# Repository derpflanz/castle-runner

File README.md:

# castle-runner

This is my hobby project in making a 6502 based 8-bit computer from scratch. The end goal is to have it run Castle Runner, a game I made many moons ago.

# CR Assembler

Castle Runner is built from scratch, including the assembler (new version, written in C). I created my own assembly language dialect to assemble the machine language code. That ML can then be written to a EEPROM. For which I built my own EEPROM programmer.

## Layout

By default, the RESET vector is set to $8000, which is the start of the ROM in the CR001 computer. The VirtualCR001 uses that as well by default. When programming the EEPROM, this vector is sent as the first two bytes and stored in $FFFC/$FFFD in the ROM.

Note that the assembler can have a DATA section at the start, which will cause to use another RESET vector to be written at the start of the .hex file.

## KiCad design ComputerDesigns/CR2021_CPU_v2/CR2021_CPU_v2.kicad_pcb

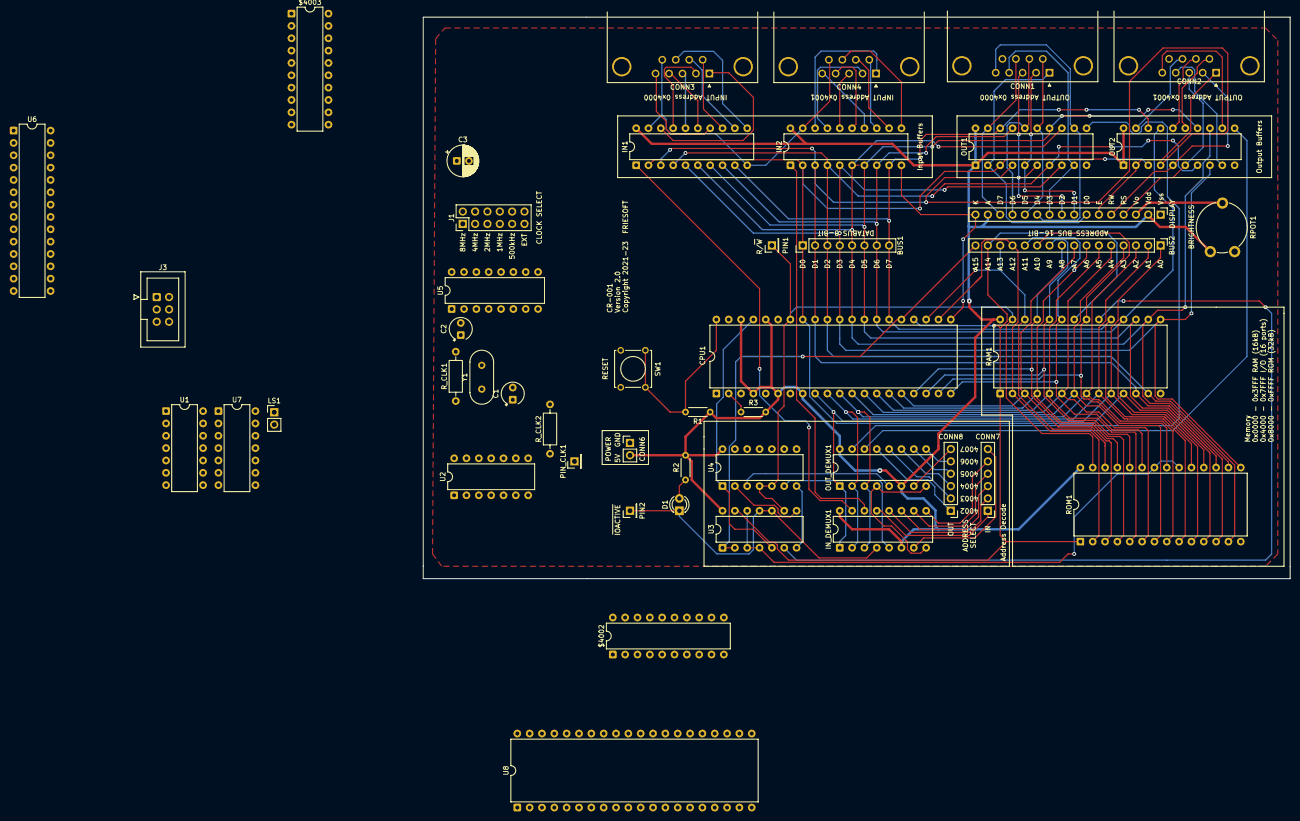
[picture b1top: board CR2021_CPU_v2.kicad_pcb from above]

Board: 2 copper layers, 178.4 x 115.6 mm, 47 parts (0 on the bottom side), 99 nets.

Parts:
$4002, $4003: 74LS273; DIP-20_W7.62mm
BUS1: DATABUS_8BIT; PinHeader_1x08_P2.54mm_Vertical
BUS2: ADDRBUS_16BIT; PinHeader_1x16_P2.54mm_Vertical
C1, C2: 22pF; CP_Radial_Tantal_D4.5mm_P2.50mm
C3: 100uF; CP_Radial_D6.3mm_P2.50mm
CONN1: OUT1; DSUB-9_Male_Horizontal_P2.77x2.84mm_EdgePinOffset9.90mm_Hou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
CONN2: OUT2; DSUB-9_Male_Horizontal_P2.77x2.84mm_EdgePinOffset9.90mm_Hou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
CONN3: IN1; DSUB-9_Male_Horizontal_P2.77x2.84mm_EdgePinOffset9.90mm_Hou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
CONN4: IN2; DSUB-9_Male_Horizontal_P2.77x2.84mm_EdgePinOffset9.90mm_Hou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
CONN5: Display; PinHeader_1x16_P2.54mm_Vertical
CONN6: +5V; PinHeader_1x02_P2.54mm_Vertical
CONN7: ADDRSEL_IN; PinHeader_1x06_P2.54mm_Vertical
CONN8: ADDRSEL_OUT; PinHeader_1x06_P2.54mm_Vertical
CPU1: WD65C02S; DIP-40_W15.24mm
D1: IO_Active; LED_D3.0mm
IN1, IN2: 74LS540; DIP-20_W7.62mm
IN_DEMUX1: 74LS138; DIP-16_W7.62mm
J1: Conn_02x06_Odd_Even; PinHeader_2x06_P2.54mm_Vertical
J3: Atmega328 Programmer Interface; IDC-Header_2x03_P2.54mm_Vertical
LS1: Speaker; PinHeader_1x02_P2.54mm_Vertical
OUT1, OUT2: 74LS273; DIP-20_W7.62mm
OUT_DEMUX1: 74LS138; DIP-16_W7.62mm
PIN1: R/!W; PinHeader_1x01_P2.54mm_Vertical
PIN2: !IO_Active; PinHeader_1x01_P2.54mm_Vertical
PIN_CLK1: EXT_CLK; PinHeader_1x01_P2.54mm_Vertical
R1: 1k; R_Axial_DIN0204_L3.6mm_D1.6mm_P5.08mm_Horizontal
R2: 330; R_Axial_DIN0204_L3.6mm_D1.6mm_P5.08mm_Horizontal
R3: 3.3k; R_Axial_DIN0204_L3.6mm_D1.6mm_P5.08mm_Horizontal
RAM1: 32 kB RAM; DIP-28_W15.24mm
ROM1: ROM ZIF Socket; DIP-28_W15.24mm
RPOT1: 10k; Potentiometer_Piher_PT-10-V10_Vertical
R_CLK1: 10M; R_Axial_DIN0207_L6.3mm_D2.5mm_P10.16mm_Horizontal
R_CLK2: 22; R_Axial_DIN0207_L6.3mm_D2.5mm_P10.16mm_Horizontal
SW1: RESET; SW_Tactile_Straight_KSL0Axx1LFTR
U1, U7: LM324; DIP-14_W7.62mm
U2: 74HCU04; DIP-14_W7.62mm
U3, U4: 7400; DIP-14_W7.62mm
U5: 74LS163; DIP-16_W7.62mm
U6: ATmega328-P; DIP-28_W7.62mm
U8: W65C22NxP; DIP-40_W15.24mm
Y1: Crystal 8MHz; Crystal_HC18-U_Vertical

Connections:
$4002_OUT: $4002.11 (Cp), CONN8.1, OUT_DEMUX1.13 (O2), U6.4 (PD2)
$4003_OUT: $4003.11 (Cp), CONN8.2, OUT_DEMUX1.12 (O3), U6.5 (PD3)
+5V: $4002.1 (~Mr), $4002.20 (VCC), $4003.1 (~Mr), $4003.20 (VCC), C3.1, CONN5.2, CONN5.15, CONN6.2, CPU1.4 (~IRQ), CPU1.6 (~NMI), CPU1.8 (VCC), CPU1.36 (BE), CPU1.38 (~SO), IN1.20 (VCC), IN2.20 (VCC), IN_DEMUX1.6 (E3), IN_DEMUX1.16 (VCC), J3.2 (VCC), OUT1.1 (~Mr), OUT1.20 (VCC), OUT2.1 (~Mr), OUT2.20 (VCC), OUT_DEMUX1.6 (E3), OUT_DEMUX1.16 (VCC), R1.1, R2.2, R3.2, RAM1.28 (VCC), ROM1.28 (VCC), RPOT1.3, U1.4 (V+), U2.14 (VCC), U3.14 (VCC), U4.14 (VCC), U5.1 (~MR), U5.7 (CEP), U5.9 (~PE), U5.10 (CET), U5.16 (VCC), U6.7 (VCC), U6.20 (AVCC)
/$4000_IN: IN1.1 (G1), IN_DEMUX1.15 (O0)
/$4000_OUT: OUT1.11 (Cp), OUT_DEMUX1.15 (O0)
/$4001_IN: IN2.1 (G1), IN_DEMUX1.14 (O1)
/$4001_OUT: OUT2.11 (Cp), OUT_DEMUX1.14 (O1)
/A14: BUS2.15, CPU1.24 (A14), RAM1.1 (A14), RAM1.22 (~OE), ROM1.1 (A14), U3.13
/A15: BUS2.16, CPU1.25 (A15), U3.1, U3.2
/Sound/PWM_Sound_Out_Voice2: J3.4 (MOSI), U6.17 (PB3)
CLK: CPU1.37 (PHI2), J1.2, J1.4, J1.6, J1.8, J1.10, J1.12, U3.5, U3.9
DATA0: $4002.3 (D0), $4003.3 (D0), BUS1.1, CPU1.33 (D0), IN1.18 (Y0), IN2.18 (Y0), OUT1.3 (D0), OUT2.3 (D0), RAM1.11 (Q0), ROM1.11 (D0), U6.23 (PC0), U8.33 (D0)
DATA1: $4002.4 (D1), $4003.4 (D1), BUS1.2, CPU1.32 (D1), IN1.17 (Y1), IN2.17 (Y1), OUT1.4 (D1), OUT2.4 (D1), RAM1.12 (Q1), ROM1.12 (D1), U6.24 (PC1), U8.32 (D1)
DATA2: $4002.7 (D2), $4003.7 (D2), BUS1.3, CPU1.31 (D2), IN1.16 (Y2), IN2.16 (Y2), OUT1.7 (D2), OUT2.7 (D2), RAM1.13 (Q2), ROM1.13 (D2), U6.25 (PC2), U8.31 (D2)
DATA3: $4002.8 (D3), $4003.8 (D3), BUS1.4, CPU1.30 (D3), IN1.15 (Y3), IN2.15 (Y3), OUT1.8 (D3), OUT2.8 (D3), RAM1.15 (Q3), ROM1.15 (D3), U6.26 (PC3), U8.30 (D3)
DATA4: $4002.13 (D4), $4003.13 (D4), BUS1.5, CPU1.29 (D4), IN1.14 (Y4), IN2.14 (Y4), OUT1.13 (D4), OUT2.13 (D4), RAM1.16 (Q4), ROM1.16 (D4), U6.27 (PC4), U8.29 (D4)
DATA5: $4002.14 (D5), $4003.14 (D5), BUS1.6, CPU1.28 (D5), IN1.13 (Y5), IN2.13 (Y5), OUT1.14 (D5), OUT2.14 (D5), RAM1.17 (Q5), ROM1.17 (D5), U6.28 (PC5), U8.28 (D5)
DATA6: $4002.17 (D6), $4003.17 (D6), BUS1.7, CPU1.27 (D6), IN1.12 (Y6), IN2.12 (Y6), OUT1.17 (D6), OUT2.17 (D6), RAM1.18 (Q6), ROM1.18 (D6), U6.2 (PD0), U8.27 (D6)
DATA7: $4002.18 (D7), $4003.18 (D7), BUS1.8, CPU1.26 (D7), IN1.11 (Y7), IN2.11 (Y7), OUT1.18 (D7), OUT2.18 (D7), RAM1.19 (Q7), ROM1.19 (D7), U6.3 (PD1), U8.26 (D7)
GND: $4002.10 (GND), $4003.10 (GND), C1.2, C2.2, C3.2, CONN1.9, CONN2.9, CONN3.9, CONN4.9, CONN5.1, CONN5.16, CONN6.1, CPU1.21 (GND), IN1.10 (GND), IN1.19 (G2), IN2.10 (GND), IN2.19 (G2), IN_DEMUX1.8 (GND), J3.6 (GND), LS1.2, OUT1.10 (GND), OUT2.10 (GND), OUT_DEMUX1.8 (GND), RAM1.14 (GND), ROM1.14 (GND), RPOT1.1, SW1.2 (B), U1.11 (V-), U2.7 (GND), U3.7 (GND), U4.7 (GND), U5.3 (D0), U5.4 (D1), U5.5 (D2), U5.6 (D3), U5.8 (GND), U6.8 (GND), U6.22 (GND)
unnamed: BUS2.1, CPU1.9 (A0), IN_DEMUX1.1 (A0), OUT_DEMUX1.1 (A0), RAM1.10 (A0), ROM1.10 (A0)
unnamed: BUS2.2, CPU1.10 (A1), IN_DEMUX1.2 (A1), OUT_DEMUX1.2 (A1), RAM1.9 (A1), ROM1.9 (A1)
unnamed: BUS2.3, CPU1.11 (A2), IN_DEMUX1.3 (A2), OUT_DEMUX1.3 (A2), RAM1.8 (A2), ROM1.8 (A2)
unnamed: BUS2.4, CPU1.12 (A3), RAM1.7 (A3), ROM1.7 (A3)
unnamed: BUS2.5, CPU1.13 (A4), RAM1.6 (A4), ROM1.6 (A4)
unnamed: BUS2.6, CPU1.14 (A5), RAM1.5 (A5), ROM1.5 (A5)
unnamed: BUS2.7, CPU1.15 (A6), RAM1.4 (A6), ROM1.4 (A6)
unnamed: BUS2.8, CPU1.16 (A7), RAM1.3 (A7), ROM1.3 (A7)
unnamed: BUS2.9, CPU1.17 (A8), RAM1.25 (A8), ROM1.25 (A8)
unnamed: BUS2.10, CPU1.18 (A9), RAM1.24 (A9), ROM1.24 (A9)
unnamed: BUS2.11, CPU1.19 (A10), RAM1.21 (A10), ROM1.21 (A10)
unnamed: BUS2.12, CPU1.20 (A11), RAM1.23 (A11), ROM1.23 (A11)
unnamed: BUS2.13, CPU1.22 (A12), RAM1.2 (A12), ROM1.2 (A12)
unnamed: BUS2.14, CPU1.23 (A13), RAM1.26 (A13), ROM1.26 (A13)
unnamed: C1.1, R_CLK1.1, U2.9, Y1.1
unnamed: C2.1, R_CLK1.2, R_CLK2.2, Y1.2
unnamed: CONN1.1, CONN5.7, OUT1.2 (Q0)
unnamed: CONN1.2, CONN5.8, OUT1.5 (Q1)
unnamed: CONN1.3, CONN5.9, OUT1.6 (Q2)
unnamed: CONN1.4, CONN5.10, OUT1.9 (Q3)
unnamed: CONN1.5, CONN5.11, OUT1.12 (Q4)
unnamed: CONN1.6, CONN5.12, OUT1.15 (Q5)
unnamed: CONN1.7, CONN5.13, OUT1.16 (Q6)
unnamed: CONN1.8, CONN5.14, OUT1.19 (Q7)
unnamed: CONN2.1, CONN5.6, OUT2.2 (Q0)
unnamed: CONN2.2, CONN5.5, OUT2.5 (Q1)
unnamed: CONN2.3, CONN5.4, OUT2.6 (Q2)
unnamed: CONN2.4, OUT2.9 (Q3)
unnamed: CONN2.5, OUT2.12 (Q4)
unnamed: CONN2.6, OUT2.15 (Q5)
unnamed: CONN2.7, OUT2.16 (Q6)
unnamed: CONN2.8, OUT2.19 (Q7)
unnamed: CONN3.1, IN1.2 (A0)
unnamed: CONN3.2, IN1.3 (A1)
unnamed: CONN3.3, IN1.4 (A2)
unnamed: CONN3.4, IN1.5 (A3)
unnamed: CONN3.5, IN1.6 (A4)
unnamed: CONN3.6, IN1.7 (A5)
unnamed: CONN3.7, IN1.8 (A6)
unnamed: CONN3.8, IN1.9 (A7)
unnamed: CONN4.1, IN2.2 (A0)
unnamed: CONN4.2, IN2.3 (A1)
unnamed: CONN4.3, IN2.4 (A2)
unnamed: CONN4.4, IN2.5 (A3)
unnamed: CONN4.5, IN2.6 (A4)
unnamed: CONN4.6, IN2.7 (A5)
unnamed: CONN4.7, IN2.8 (A6)
unnamed: CONN4.8, IN2.9 (A7)
unnamed: CONN5.3, RPOT1.2
unnamed: CONN7.1, IN_DEMUX1.13 (O2)
unnamed: CONN7.2, IN_DEMUX1.12 (O3)
unnamed: CONN7.3, IN_DEMUX1.11 (O4)
unnamed: CONN7.4, IN_DEMUX1.10 (O5)
unnamed: CONN7.5, IN_DEMUX1.9 (O6)
unnamed: CONN7.6, IN_DEMUX1.7 (O7)
unnamed: CONN8.3, OUT_DEMUX1.11 (O4)
unnamed: CONN8.4, OUT_DEMUX1.10 (O5)
unnamed: CONN8.5, OUT_DEMUX1.9 (O6)
unnamed: CONN8.6, OUT_DEMUX1.7 (O7)
unnamed: CPU1.2 (RDY), R3.1
unnamed: CPU1.40 (~RESET), R1.2, SW1.1 (A)
unnamed: D1.2 (A), R2.1
unnamed: D1.1 (K), IN_DEMUX1.4 (E1), OUT_DEMUX1.4 (E1), PIN2.1, U3.11
unnamed: IN_DEMUX1.5 (E2), U3.10, U4.6
unnamed: J1.1, R_CLK2.1, U2.8, U5.2 (CP)
unnamed: J1.3, U5.14 (Q0)
unnamed: J1.5, U5.13 (Q1)
unnamed: J1.7, U5.12 (Q2)
unnamed: J1.9, U5.11 (Q3)
unnamed: J1.11, PIN_CLK1.1
unnamed: J3.1 (MISO), U6.18 (PB4)
unnamed: J3.5 (RST), U6.1 (~RESET/PC6)
unnamed: J3.3 (SCK), U6.19 (PB5)
unnamed: LS1.1, U1.7
unnamed: OUT_DEMUX1.5 (E2), U3.8
unnamed: RAM1.20 (~CS), U3.6
unnamed: ROM1.20 (~CS), ROM1.22 (~OE), U3.3, U3.4, U3.12
unnamed: U1.5 (+), U7.1, U7.2 (-)
R/!W: CPU1.34 (R/~W), PIN1.1, RAM1.27 (~WE), ROM1.27 (~WE), U4.4, U4.5

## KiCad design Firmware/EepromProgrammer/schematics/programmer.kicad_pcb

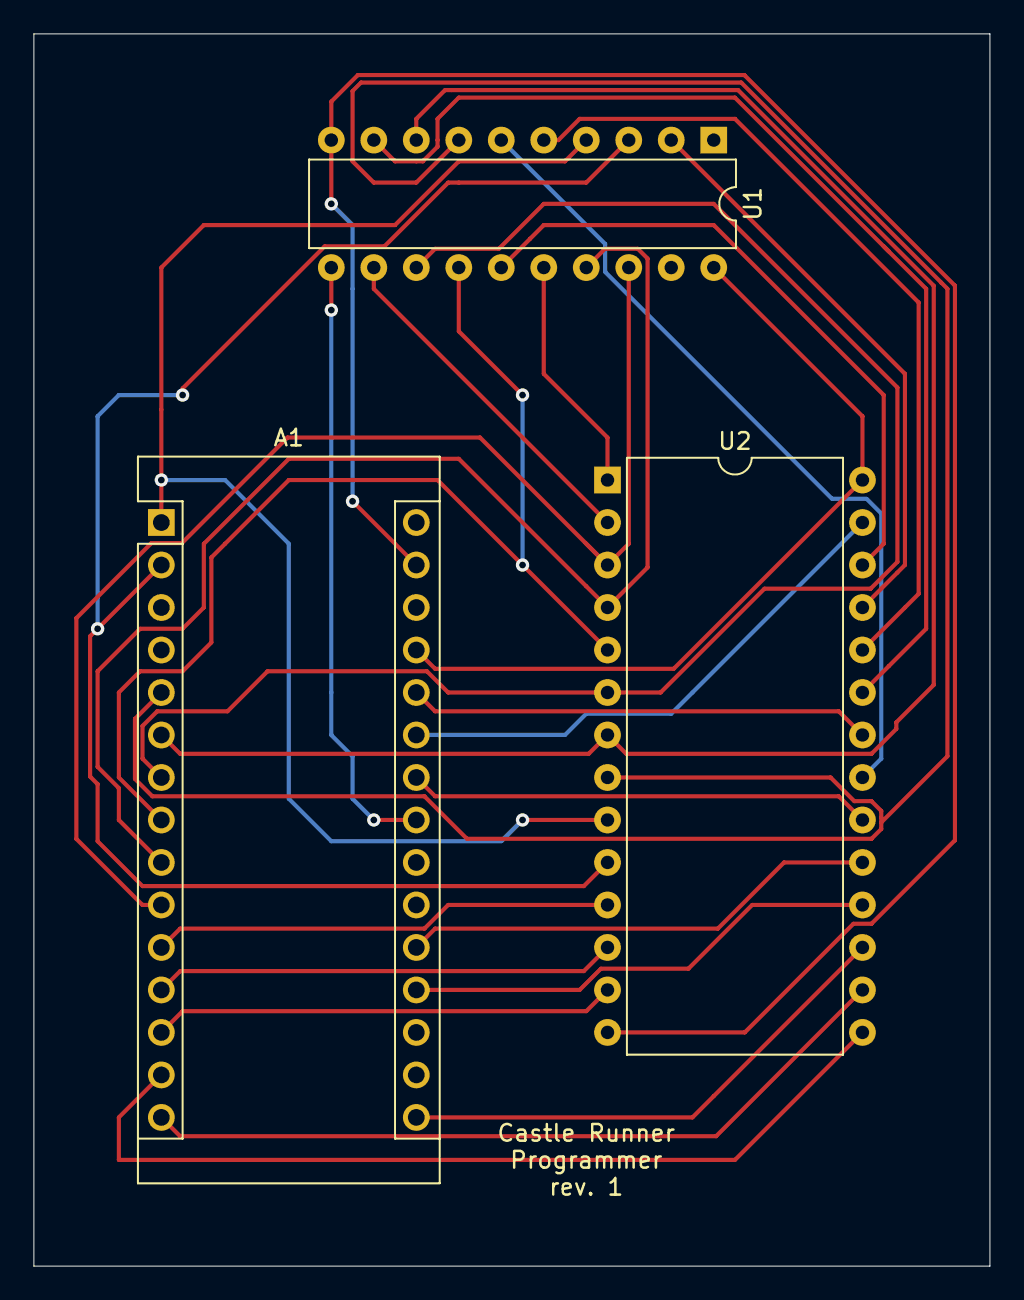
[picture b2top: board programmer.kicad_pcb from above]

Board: 2 copper layers, 57.2 x 73.7 mm, 3 parts (0 on the bottom side), 29 nets.

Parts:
A1: Arduino_Nano_v3.x; Arduino_Nano
U1: 74LS273; DIP-20_W7.62mm
U2: KM62256CLP; DIP-28_W15.24mm

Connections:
unnamed: A1.1, U1.4, U2.9
unnamed: A1.2, U1.3, U2.10
unnamed: A1.5, U1.7, U2.8
unnamed: A1.6, U1.8, U2.7
unnamed: A1.7, U1.13, U2.6
unnamed: A1.8, U1.14, U2.5
unnamed: A1.9, U1.17, U2.4
unnamed: A1.10, U1.18, U2.3
unnamed: A1.11, U2.11
unnamed: A1.12, U2.12
unnamed: A1.13, U2.13
unnamed: A1.14, U2.15
unnamed: A1.15, U2.16
unnamed: A1.16, U2.17
unnamed: A1.19, U2.18
unnamed: A1.20, U2.19
unnamed: A1.23, U1.11
unnamed: A1.24, U2.20
unnamed: A1.25, U2.27
unnamed: A1.26, U2.22
unnamed: A1.27, U1.1, U1.20, U2.28
unnamed: A1.29, U1.10, U2.14
unnamed: U1.2, U2.25
unnamed: U1.5, U2.24
unnamed: U1.6, U2.21
unnamed: U1.9, U2.23
unnamed: U1.12, U2.2
unnamed: U1.15, U2.26
unnamed: U1.16, U2.1

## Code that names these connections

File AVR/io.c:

#include "io.h"

// PD4 = ~R/W
// PD5 = CTRL_REG
// PD6 = DATA_REG
// PC0-PC5,PD0-PD1 = DATA

void init_io() {
    DDRD &= ~(
        // Set R/!W, DR and CR as INPUTs (no pullup resistor)
        (1 << DDD2) | (1 << DDD3) | (1 << DDD4) | 

        // Set D6 and D7 as INPUTs (no pullup)
        (1 << DDD0) | (1 << DDD1)
    );

    DDRC &= ~(
        // Set D0-5 as INPUTs (no pullup)
        (1 << DDC0) | (1 << DDC1) | (1 << DDC2) | 
        (1 << DDC3) | (1 << DDC4) | (1 << DDC5) 
    )
}

uint8_t rw() {
    return (PIND & (1 << PD4) ? 1 : 0);
}

uint8_t dr() {
    return (PIND & (1 << PD2) ? 1 : 0);
}

uint8_t cr() {
    return (PIND & (1 << PD3) ? 1 : 0);
}

uint8_t data() {
    uint8_t d = 0;

    // read PC0-5
    d |= (PINC & 0b00111111);
    // read PD0-1
    d |= ((PIND & 0b00000011) << 6);

    return d;
}

struct state read_state() {
    struct state io_state;

    io_state.rw = rw();
    io_state.dr = dr();
    io_state.cr = cr();
    io_state.data = data();
    
    io_state.reg_select = REG_NONE;

    if (io_state.dr == 1 && io_state.cr == 0) {
        io_state.reg_select = REG_DATA;
    }

    if (io_state.dr == 0 && io_state.cr == 1) {
        io_state.reg_select = REG_CTRL;
    }

    return io_state;
}

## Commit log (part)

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2021-01-10 implement EEPROM read
2021-01-10 add eeprom.py
2021-01-17 Working version
2021-01-17 cleanup
2021-01-17 Fix SYNC at startup
2021-01-30 Add port to command
2021-01-30 Bigfixes
2021-01-30 Write 0x8000 as starting vector to 0xFFFC, do we do not need to upload all 32k
2021-01-30 Add header in comm; verify on write always
2021-01-30 Add 8 output LEDs
2021-01-31 Use 0x7FFA as output to LEDs
2021-01-31 Add counter assembly file
2021-01-31 Add assembler
2021-02-07 Add opcodes + test
2021-02-07 Add LDA(imme)
2021-02-07 Add _to_bytes to translate operand into hex bytes
2021-02-07 Add counter.asm; generate binary codes
2021-02-07 Start work on label support
2021-02-07 Implement labels
2021-02-13 Add I/O2 to monitor
2021-02-13 Add JSR and RTS
2021-02-13 Add ASCII token support
2021-02-13 Rewrite monitor
2021-02-13 fixes
2021-02-13 minor change to ASCII output
2021-02-14 Remove empty line
2021-02-14 Reorganise
2021-02-14 Add build script for easy Arduino builds
2021-02-14 rename sketch
2021-02-14 Add assemble.sh
2021-02-14 clenup
2021-03-01 Add diffing monitor
2021-04-04 Monitor fixes
2021-04-04 Add BRK / LDX
2021-04-04 Add location address
2021-04-04 Ignore non-code
2021-04-04 Implement preprocessor for assembler
2021-04-04 Implement INX
2021-04-04 Add absolute indirect Y addressing mode
2021-04-04 Add LDY
2021-04-04 Cleanups
2021-04-04 Cleanups and new opcodes
2021-04-05 Read first two bytes as RESB
2021-04-05 Implement concat
2021-04-05 Add target
2021-04-05 Refactor
2021-04-05 Add stuff
2021-04-05 Cool things
2021-04-17 Remove serial port processing from interrupt handling
2021-04-17 Add notes
2021-04-17 Remove old code
2021-04-17 Add TXS
2021-04-17 Add SEI and CLD
2021-10-17 monitor updates
2021-10-17 add absolute addressing for INC
2021-10-17 add opcode matrix
2021-10-17 Implement generic opcode creator
2021-10-17 implement first column of opcodes (pg 22)
2021-10-17 add comment
2021-10-24 Implement all opcodes through matrix generator
2022-02-13 Add arduino control for new board
2022-02-13 misc
2022-02-13 monitor
2022-02-13 robot arduino
2022-02-13 soundchip arduino
2022-02-13 trigger virtual when no eeprom found
2022-02-13 complete assembler
2022-02-13 fix programmer
2022-02-13 Add CR001 virtual machine
2022-02-13 ignore
2022-02-15 add makefile
2022-02-15 Add LCD window
2022-02-15 Refactor ui calls
2022-02-15 Add LCD
2022-02-15 remove unused function
2022-02-15 update makefile Wall Werror
2022-02-15 refactor memory functions
2022-02-15 refactor functions
2022-02-15 wire inputs on lcd
2022-02-15 fix write into ROM
2022-02-15 show ROM in memory view
2022-02-15 Add DEC for ACC addressing mode
2022-02-19 Add warning for undocumented opcodes
2022-02-19 Add CR001 ROM code
2022-02-19 Add gamecode
2022-02-19 Add GameCode makefile
2022-02-19 Add Tools root Makefile
2022-02-19 Add extra doc to ROM
2022-02-19 Parametrise mem view
2022-02-19 Add SP to stack view
2022-02-19 Splash in Game
2022-02-19 Implement second log (I/O)
2022-02-21 Refactor privates
2022-02-21 Add ROM view with PC
2022-02-21 Add info to ROM view
2022-02-21 Add run
2022-02-21 Sleep when idle
2022-02-21 Speed up window stuff
2022-02-21 Fix lexer to correctly read ZPINDX/Y
2022-02-21 Add test run to makefile
2022-02-21 Add disassembler to running logs
2022-04-11 Add target to build HEX file
2022-04-11 Change log name
2022-04-11 Add absolute addressing mode log
2022-04-11 Add rel and indy
2022-04-18 Implement breakpoint for BRK opcode
2022-04-18 Update documentation
2022-04-18 Add !break directive scaffolding
2022-04-18 Create breakpoints file
2022-04-18 Remove assemble.sh (use makefile instead)
2022-04-18 Implement debug file
2022-04-18 Read breakpoints into array
2022-04-23 Add red color for breakpoints
2022-04-23 Add scaffolding for address list
2022-04-23 use an uint16_t array as highlight list
2022-04-23 Show breakpoints in ROM
2022-04-23 Stop when breakpoint hit
2022-04-30 fix displaygotoxy
2022-04-30 use letters in flag register
2022-04-30 implement dec2ascii
2022-05-07 Better monitor
2022-05-07 Implement joystick in VM
2022-05-07 First basic game!
2022-05-14 Calc new location
2022-05-14 Limit external walls
2023-05-07 Add video signal experiments
2023-05-07 change CR1 tool to platformio
2023-07-16 update PIO
2023-07-16 Add IRQ handler
2023-07-16 Migratie EEPROM Programmer to PlatformIO
2023-07-22 Implement header struct
2023-07-22 Update command line help message
2023-07-22 Remove magic command numbers
2023-07-22 Send the RESB vector in the header
2023-07-22 Read RESB in header
2023-07-22 Add start_address to header
2023-07-22 Make printing nice
2023-07-22 Fix layout of bytes
2023-07-22 Remove RESB from data stream
2023-07-22 Write vector before data
2023-09-16 Write IRQ vector to ASM file
2023-10-08 Receive and write IRQ vector into EEPROM
2023-10-08 Send IRQ vector to programmer
2023-10-08 Add program target to generic Makefile
2023-10-08 Enable IRQ interrupts
2023-10-08 Update IRQ handler
2023-11-10 Process IRQ vector in VM
2023-11-11 Add new CR2 ROM
2023-11-11 Add video rom in VM
2023-11-11 build CR002 ROM
2023-11-11 Update XY to ROWCOL
2023-11-11 Set row.,col
2023-11-11 Remove init display --> goes to IRQ
2023-11-11 Implement direct location
2023-11-11 Add EA to VM
2023-11-11 Move regexes around, so it works
2023-11-11 Fix addressing in ,X
2023-11-11 Show printable chars
2023-11-11 Implement displaystring
2023-11-11 Improve error messages
2023-11-11 Add dec2ascii in CR002
2023-11-11 Add IRQ suppor to VM
2023-12-09 Make LargeDisplay work
2023-12-09 Implement LargeDisplay reset
2023-12-16 Add display initialization
2023-12-31 Implement new display calls
2023-12-31 Fix RESB vector
2023-12-31 Add 3rd target
2023-12-31 Display tests
2023-12-31 Io tests
2024-01-04 Make Mem a little larger in virtual CR
2024-01-04 Implement video blitses
2024-01-04 Add video routines
2024-01-04 Implement GotoXY
2024-01-04 Implement WriteString
2024-01-06 Add write-data command
2024-01-06 Add start_address to write
2024-01-06 Use existing codes
2024-01-06 Update makefile to use write-code
2024-01-06 Use start_address is writing
2024-01-06 Implement data write in programmer
2024-01-06 Implement make target for program-data
2024-01-06 Test update
2024-01-06 Implement write graph screen
2024-01-06 Indent to enable folding
2024-01-06 Implement cursors
2024-01-06 Test code
2024-01-13 Fix WriteGraphScreen
2024-01-15 Fix off-by-one error
2024-01-15 Increase graph pointer by 1 after write
2024-01-20 Update test code
2024-01-20 Running tests scaffolding
2024-01-20 Add testfile check
2024-01-20 Fix XY-ROWCOL calculations
2024-02-04 Add symbols file
2024-02-04 Set correct Video RAM address
2024-02-04 Implement video ram paging
2024-02-04 Implement (zp) addressing mode for STA
2024-02-04 Write $C000 to video RAM
2024-02-04 setup pixelart
2024-02-10 Write data to hex file
2024-02-10 ignore ascii datafile
2024-02-10 Basic movement
2024-02-10 Eat gold
2024-02-11 Add display showing VMEM
2024-02-11 Add debug tools
2024-02-11 Add missing opcodes
2024-02-11 Remove emul code
2024-02-11 Implement ignore JSR
2024-02-17 Fix when no ignores given
2024-02-24 sound stuff
2024-02-24 Fix when no debuginfo file given
2024-02-24 Move assembler to class
2024-02-24 Fix main
2024-02-24 Implement variable for absolute addressing
2024-02-24 Revert "misc"
    This reverts commit 0c967395c46827787a51dddccc545d5ac6a2647c.
2024-02-24 Process variables before lexing
2024-02-24 minor rom changes
2024-02-24 Implement ignores
2024-03-09 Add new assembler files
2024-03-09 Add opcode matrixes
2024-03-09 Add error counter
2024-03-23 move identifier ll into own C file
2024-03-23 Add all addressing modes
2024-03-23 add clean
2024-03-23 fix parser for ,x and ,y
2024-03-23 implement branch mmnemonics
2024-03-23 Add offsets
2024-03-23 implement hi/lo
2024-03-23 Fix lowerer
2024-03-29 debug stuff
2024-03-29 make ao not a pointer
2024-03-29 remove strdups
2024-03-29 Add operation to ident
2024-03-29 Make operation a token
2024-03-29 add byte and string
2024-04-01 Move opcodes to own C file
2024-04-01 Move get_address
2024-04-01 Refactor addr_offset
2024-04-01 change output
2024-04-01 add offset for operated operands
2024-04-01 add operated ident
2024-04-14 Add tree
2024-04-14 Add tree printing
2024-04-14 Implement statement for tree
2024-04-14 clean
2024-04-21 Do not use identifiers global
2024-04-21 De-globalise identifiers
2024-04-21 de-globalise statement tree
2024-04-21 remove identifier_get
2024-04-21 fix load string
2024-04-21 Add node tpye
2024-04-21 Write byte and string
2024-04-21 address arithmetic
2024-04-21 Calc operand
2024-04-21 calc operand length
2024-04-21 Implement operand output
2024-04-21 Add command line arguments
2024-04-21 add address to node
2024-05-25 Remove generic Arduino projects
2024-05-25 Implement output
2024-05-25 fix string length calc
2024-05-25 add game code compiling
2024-05-25 implement char literal
2024-05-25 update rom for new assembler
2024-05-25 add verbose options
2024-05-25 Add vectors
2024-05-25 GameCodeNG makefile
2024-05-25 implemnt ignore basics
2024-05-25 read ignores
2024-05-25 implement ignore
2024-05-25 Make startup script
2024-05-29 Implement relative addressing
2024-06-01 Improve user readable output for assembler
2024-06-01 Add variables in Game Code
2024-06-01 Fix makefiles
2025-02-23 basic sound stuff (triangle + sawtooth)
2025-02-23 add sine wave
2025-02-23 Add noise
2025-02-23 add freq to sawtooth
2025-02-23 add a lower frequency sawtooth
2025-03-02 Add fine grained frequency and 0.125ms oscilator
2025-03-08 add vs code settings
2025-03-08 add ignores
2025-03-08 tests
2025-03-08 make happy birthday
2025-03-08 add attack, decay and release
2025-03-08 Calc envelope steps
2025-03-08 basic envelope
2025-03-08 Fix timing
2025-03-08 Add speed
2025-03-08 settings
2025-03-08 tweaks
2025-03-08 sine
2025-03-08 make steps static
2025-03-08 cleanup globals
2025-03-08 dont attack adsr of 0
2025-03-08 make the amplitude 16 bit, so the envelope lengths work for larger numbers
2025-03-15 Add IOTester tool for Arduino
2025-03-15 Remove unused files
2025-03-15 Split into main and sound
2025-03-15 Move all sound code to sound.c
2025-03-15 trigger song on rw
2025-03-16 Create "start song"
2025-03-16 add clean target in makefile
2025-03-16 Move io stuff into io.c
2025-03-16 Add X to IOTester
2025-03-16 implement io_state
2025-03-16 implement register selection
2025-04-08 Only check registers
2025-04-08 Read data
2025-04-08 implement start song command
2025-04-13 Move stuff around
2025-04-13 Add everything
2025-04-13 Add readmes
2025-09-13 add sound
2025-09-13 Implement Game Over
2025-09-13 assembler bugfix
2025-09-13 Remove useless code in BRK handler in virtual machine
2025-11-01 setup basic reg/data i/o
2025-11-01 Implement 8bit registers
2025-11-01 Implement waveform select
2025-11-08 Add OC2A as 2nd voice output
2025-11-09 add params for second voice
2025-11-09 add avrdude device finder
2025-11-09 implement two voices
2025-11-09 remove cli/sei in interrupt handlers
2025-11-09 updated schematic with opamp mixer
2026-05-03 update schematics
2026-05-03 Implement verify
2026-05-09 add some VIA addresses
2026-05-09 Speed up EEPROM programmer
2026-05-09 add verify page
2026-05-09 add delay to settle
2026-05-09 remove logging from ASMNG
2026-05-09 vibe code cleanup

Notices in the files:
ComputerDesigns/CR2021_CPU_v2/CR2021_CPU_v2.kicad_pcb:
Copyright 2021-23  FRIESOFT
